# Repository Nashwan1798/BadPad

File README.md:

# BadPad
The schematics and code of my BadPad (my own custom macropad)
_______________________________________________________________________________
## Features:
- 128x32 OLED Display
- EC11 Rotary encoder (no button)
- 9 SK8612MINI-E LEDS
- 9 Keys
## CAD/ASSEMBLY
This is a picture of the full build/assembly.

_______________________________________________________________________________
## PCB

This is a picture of the PCB and I must say building the PCB was the easiest part of this project.

_______________________________________________________________________________
## CASE
A screenshot of the case, I honestly needed tons of help of AI with this one because fusion is really really confusing to use and I was not making any progress after hours of work put in.

_______________________________________________________________________________
## Schematic
a picture of the schematic

Inspired by Orpheuspad, Keybie-Hackpad, stratum-macropad.

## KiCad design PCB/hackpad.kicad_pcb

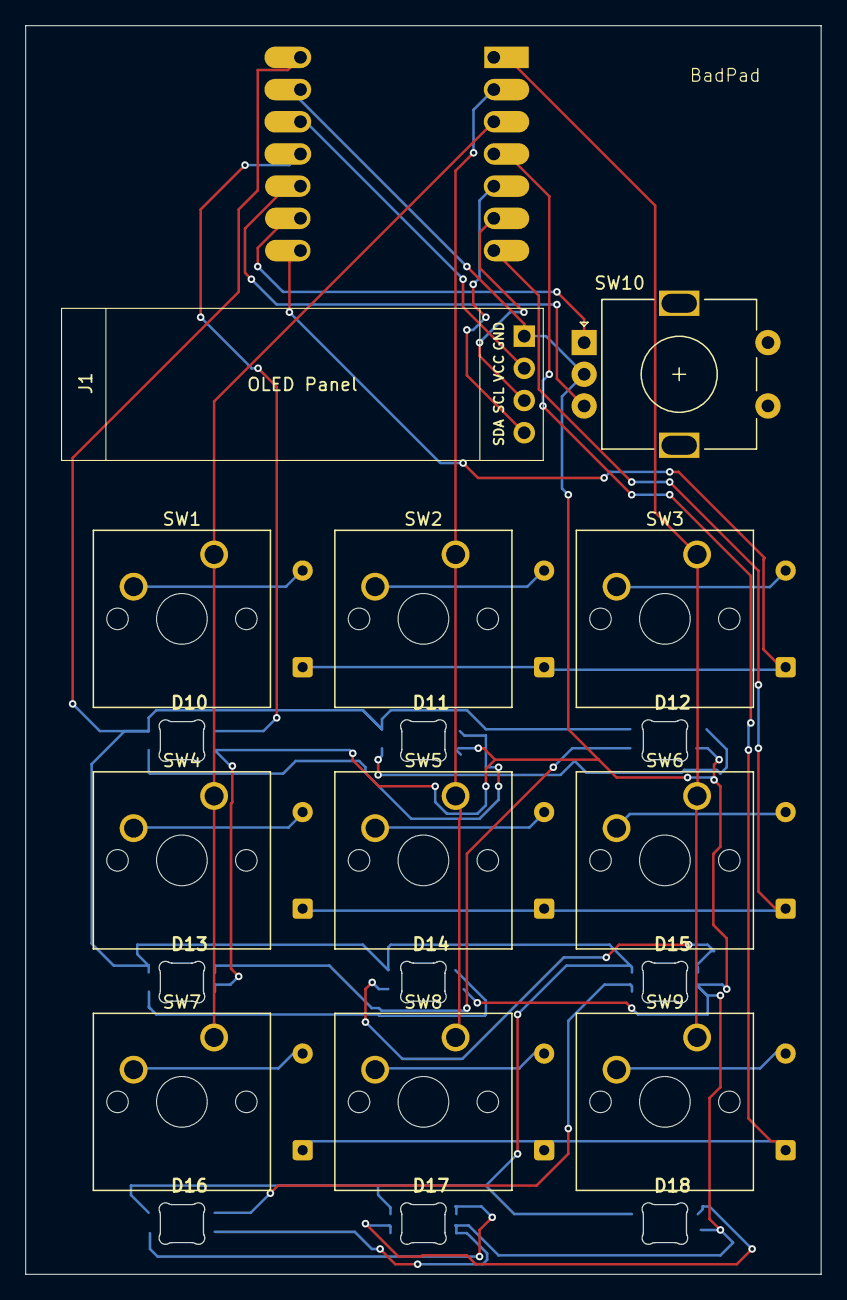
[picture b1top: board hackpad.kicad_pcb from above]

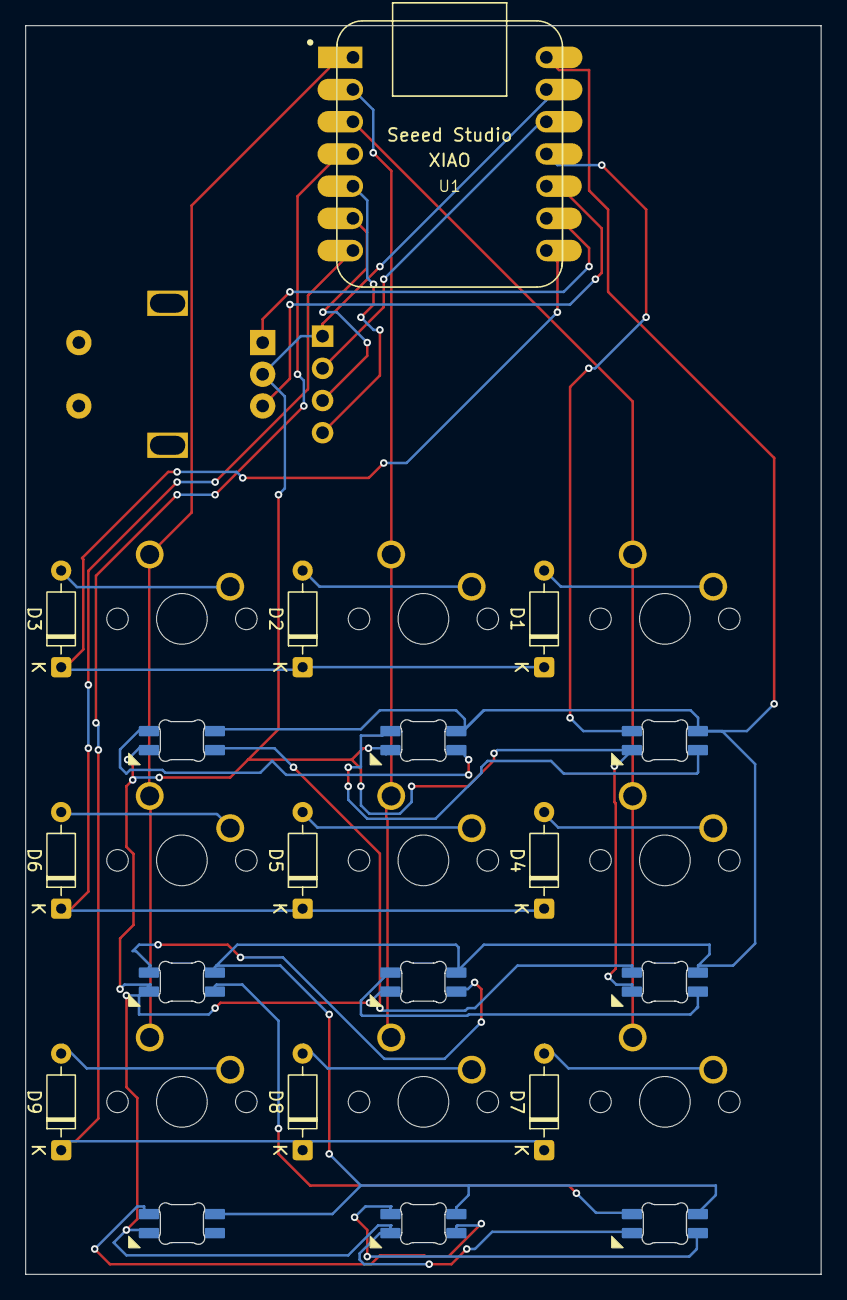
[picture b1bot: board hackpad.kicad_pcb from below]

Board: 2 copper layers, 62.7 x 98.5 mm, 30 parts (10 on the bottom side), 31 nets.

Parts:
D1, D2, D3, D4, D5, D6, D7, D8, D9: D_DO-35_SOD27_P7.62mm_Horizontal
D10, D11, D12, D13, D14, D15, D16, D17, D18: SK6812MINI-E; SK6812MINI-E_fixed_model
J1: OLED_128x32; SSD1306-0.91-OLED-4pin-128x32
SW1, SW2, SW3, SW4, SW5, SW6, SW7, SW8, SW9: SW_Push; MX_with_model
SW10: RotaryEncoder_Switch; RotaryEncoder_Alps_EC11E-Switch_Vertical_H20mm
U1: MOUDLE-SEEEDUINO-XIAO; XIAO-Generic-Hybrid-14P-2.54-21X17.8MM

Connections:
+3.3V: J1.2 (VCC), U1.12 (3V3)
+5V: D10.1 (VDD), D11.1 (VDD), D12.1 (VDD), D13.1 (VDD), D14.1 (VDD), D15.1 (VDD), D16.1 (VDD), D17.1 (VDD), D18.1 (VDD), U1.14 (5V)
Column 1: SW1.1, SW4.1, SW7.1, U1.3 (PA10_A2_D2)
Column 2: SW2.1, SW5.1, SW8.1, U1.2 (PA4_A1_D1)
Column 3: SW3.1, SW6.1, SW9.1, U1.1 (PA02_A0_D0)
GND: D10.3 (VSS), D11.3 (VSS), D12.3 (VSS), D13.3 (VSS), D14.3 (VSS), D15.3 (VSS), D16.3 (VSS), D17.3 (VSS), D18.3 (VSS), J1.1 (GND), SW10.C, U1.13 (GND)
unnamed: D1.2 (A), SW1.2
unnamed: D2.2 (A), SW2.2
unnamed: D3.2 (A), SW3.2
unnamed: D4.2 (A), SW4.2
unnamed: D5.2 (A), SW5.2
unnamed: D6.2 (A), SW6.2
unnamed: D7.2 (A), SW7.2
unnamed: D8.2 (A), SW8.2
unnamed: D9.2 (A), SW9.2
unnamed: D10.2 (DOUT), D11.4 (DIN)
unnamed: D11.2 (DOUT), D12.4 (DIN)
unnamed: D12.2 (DOUT), D13.4 (DIN)
unnamed: D13.2 (DOUT), D14.4 (DIN)
unnamed: D14.2 (DOUT), D15.4 (DIN)
unnamed: D15.2 (DOUT), D16.4 (DIN)
unnamed: D16.2 (DOUT), D17.4 (DIN)
unnamed: D17.2 (DOUT), D18.4 (DIN)
Rotary A: SW10.A, U1.9 (PA7_A8_D8_SCK)
Rotary B: SW10.B, U1.10 (PA5_A9_D9_MISO)
Row 1: D1.1 (K), D2.1 (K), D3.1 (K), U1.8 (PB09_A7_D7_RX)
Row 2: D4.1 (K), D5.1 (K), D6.1 (K), U1.7 (PB08_A6_D6_TX)
Row 3: D7.1 (K), D8.1 (K), D9.1 (K), U1.4 (PA11_A3_D3)
oled scl: J1.3 (SCL), U1.6 (PA9_A5_D5_SCL)
oled sda: J1.4 (SDA), U1.5 (PA8_A4_D4_SDA)
rgbdata: D10.4 (DIN), U1.11 (PA6_A10_D10_MOSI)

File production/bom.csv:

Designator,Footprint,Quantity,Value,LCSC Part #
"D1, D2, D3, D4, D5, D6, D7, D8, D9",D_DO-35_SOD27_P7.62mm_Horizontal,9,~,
"D10, D11, D12, D13, D14, D15, D16, D17, D18",SK6812MINI-E_fixed_model,9,SK6812MINI-E,
J1,SSD1306-0.91-OLED-4pin-128x32,1,OLED_128x32,
"SW1, SW2, SW3, SW4, SW5, SW6, SW7, SW8, SW9",MX_with_model,9,SW_Push,
SW10,RotaryEncoder_Alps_EC11E-Switch_Vertical_H20mm,1,RotaryEncoder_Switch,
U1,XIAO-Generic-Hybrid-14P-2.54-21X17.8MM,1,MOUDLE-SEEEDUINO-XIAO,
